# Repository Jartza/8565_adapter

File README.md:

# 8565_adapter
Adapter PCB to use 8565 VIC-II in place of 6569 VIC-II chips.

The adapter should also work with NTSC 8562 allowing it to be used in machines that had 6567 in them.

## License
Do whatever you wish with these -type, aka Open Hardware

## Ready-made PCBs

Order here: https://www.pcbway.com/project/shareproject/VIC_II_8565_8562_to_6569_6567_adapter.html

## PICS

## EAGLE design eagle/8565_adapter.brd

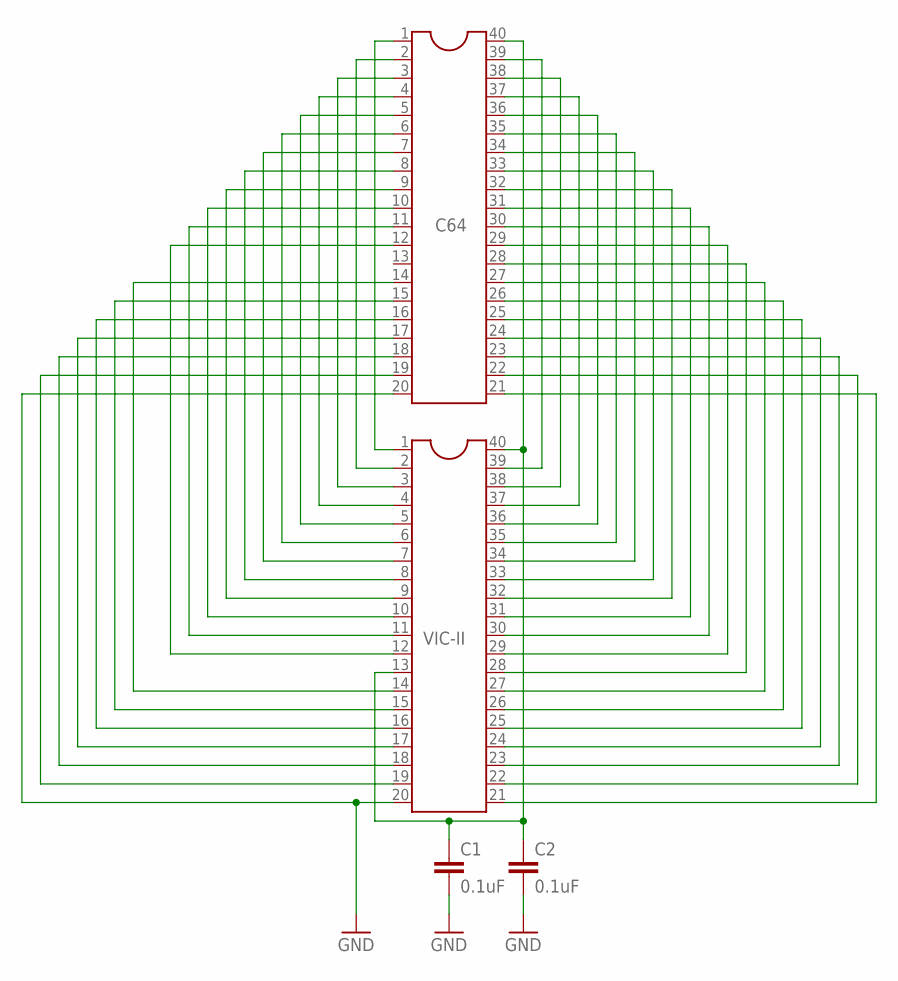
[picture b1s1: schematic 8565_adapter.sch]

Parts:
C1: 0.1uF; 0603-CAP
C2: 0.1uF; CAP-PTH-SMALLEZ
C64: DIL40NO_SILK; DIL40-TINY
VIC-II: DIL40

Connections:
GND: C1.2, C2.2, C64.20, VIC-II.20
unnamed: C1.1, C2.1, C64.40, VIC-II.13, VIC-II.40
unnamed: C64.39, VIC-II.39
unnamed: C64.38, VIC-II.38
unnamed: C64.37, VIC-II.37
unnamed: C64.36, VIC-II.36
unnamed: C64.35, VIC-II.35
unnamed: C64.34, VIC-II.34
unnamed: C64.33, VIC-II.33
unnamed: C64.32, VIC-II.32
unnamed: C64.31, VIC-II.31
unnamed: C64.30, VIC-II.30
unnamed: C64.29, VIC-II.29
unnamed: C64.28, VIC-II.28
unnamed: C64.27, VIC-II.27
unnamed: C64.26, VIC-II.26
unnamed: C64.25, VIC-II.25
unnamed: C64.24, VIC-II.24
unnamed: C64.23, VIC-II.23
unnamed: C64.22, VIC-II.22
unnamed: C64.21, VIC-II.21
unnamed: C64.2, VIC-II.2
unnamed: C64.3, VIC-II.3
unnamed: C64.4, VIC-II.4
unnamed: C64.5, VIC-II.5
unnamed: C64.6, VIC-II.6
unnamed: C64.7, VIC-II.7
unnamed: C64.8, VIC-II.8
unnamed: C64.9, VIC-II.9
unnamed: C64.10, VIC-II.10
unnamed: C64.11, VIC-II.11
unnamed: C64.12, VIC-II.12
unnamed: C64.14, VIC-II.14
unnamed: C64.15, VIC-II.15
unnamed: C64.16, VIC-II.16
unnamed: C64.17, VIC-II.17
unnamed: C64.18, VIC-II.18
unnamed: C64.19, VIC-II.19
unnamed: C64.1, VIC-II.1

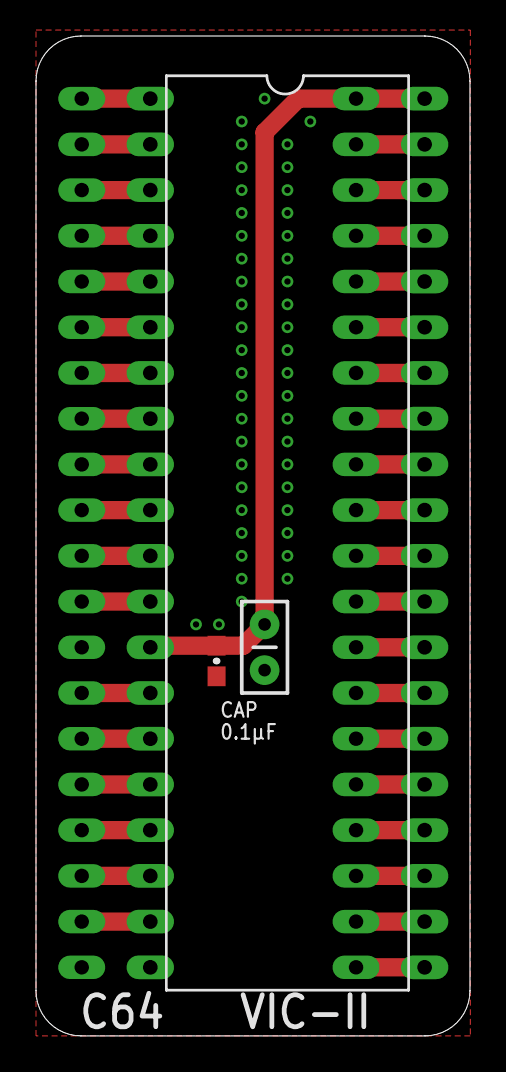
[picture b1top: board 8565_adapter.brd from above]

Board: 2 copper layers, 24.1 x 55.5 mm, 4 parts (0 on the bottom side), 39 nets.

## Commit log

2020-06-17 Add SVG
2020-06-17 Update SVG

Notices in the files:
eagle/8565_adapter.brd:
(C) 2019
parts and their libraries:
SparkFun-Capacitors: Licensing: Creative Commons ShareAlike 4.0 International - https://creativecommons.org/licenses/by-sa/4.0
